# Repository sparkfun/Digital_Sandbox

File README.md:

Digital_Sandbox
===============

[*SparkFun Digital Sandbox (SKU)*](https://www.sparkfun.com/products/12651)

he Digital Sandbox (DS) is a learning platform that engages both the software and hardware worlds.
It’s powered by a microcontroller that can interact with real-world inputs – like light or temperature sensors – while simultaneously controlling LEDs, motors, and other outputs. 

Repository Contents
-------------------

* **/Documentation** - Data files for the Digital Sandbox booklet
* **/Firmware** - Example code for the Digital Sandbox experiment guide
* **/Hardware** - Eagle design files (.brd, .sch)
* **/Production** - Production panel files (.brd)

Documentation
--------------
* **[Hookup Guide](https://learn.sparkfun.com/tutorials/digital-sandbox-arduino-companion)** - Basic hookup guide for the Digital SandBox.
* **[SparkFun Fritzing repo](https://github.com/sparkfun/Fritzing_Parts)** - Fritzing diagrams for SparkFun products.
* **[SparkFun 3D Model repo](https://github.com/sparkfun/3D_Models)** - 3D models of SparkFun products.
* **[SparkFun Graphical Datasheets](https://github.com/sparkfun/Graphical_Datasheets)** -Graphical Datasheets for various SparkFun products.

License Information
-------------------

This product is _**open source**_!

Please review the LICENSE.md file for license information.

If you have any questions or concerns on licensing, please contact techsupport@sparkfun.com.

Distributed as-is; no warranty is given.

- Your friends at SparkFun.

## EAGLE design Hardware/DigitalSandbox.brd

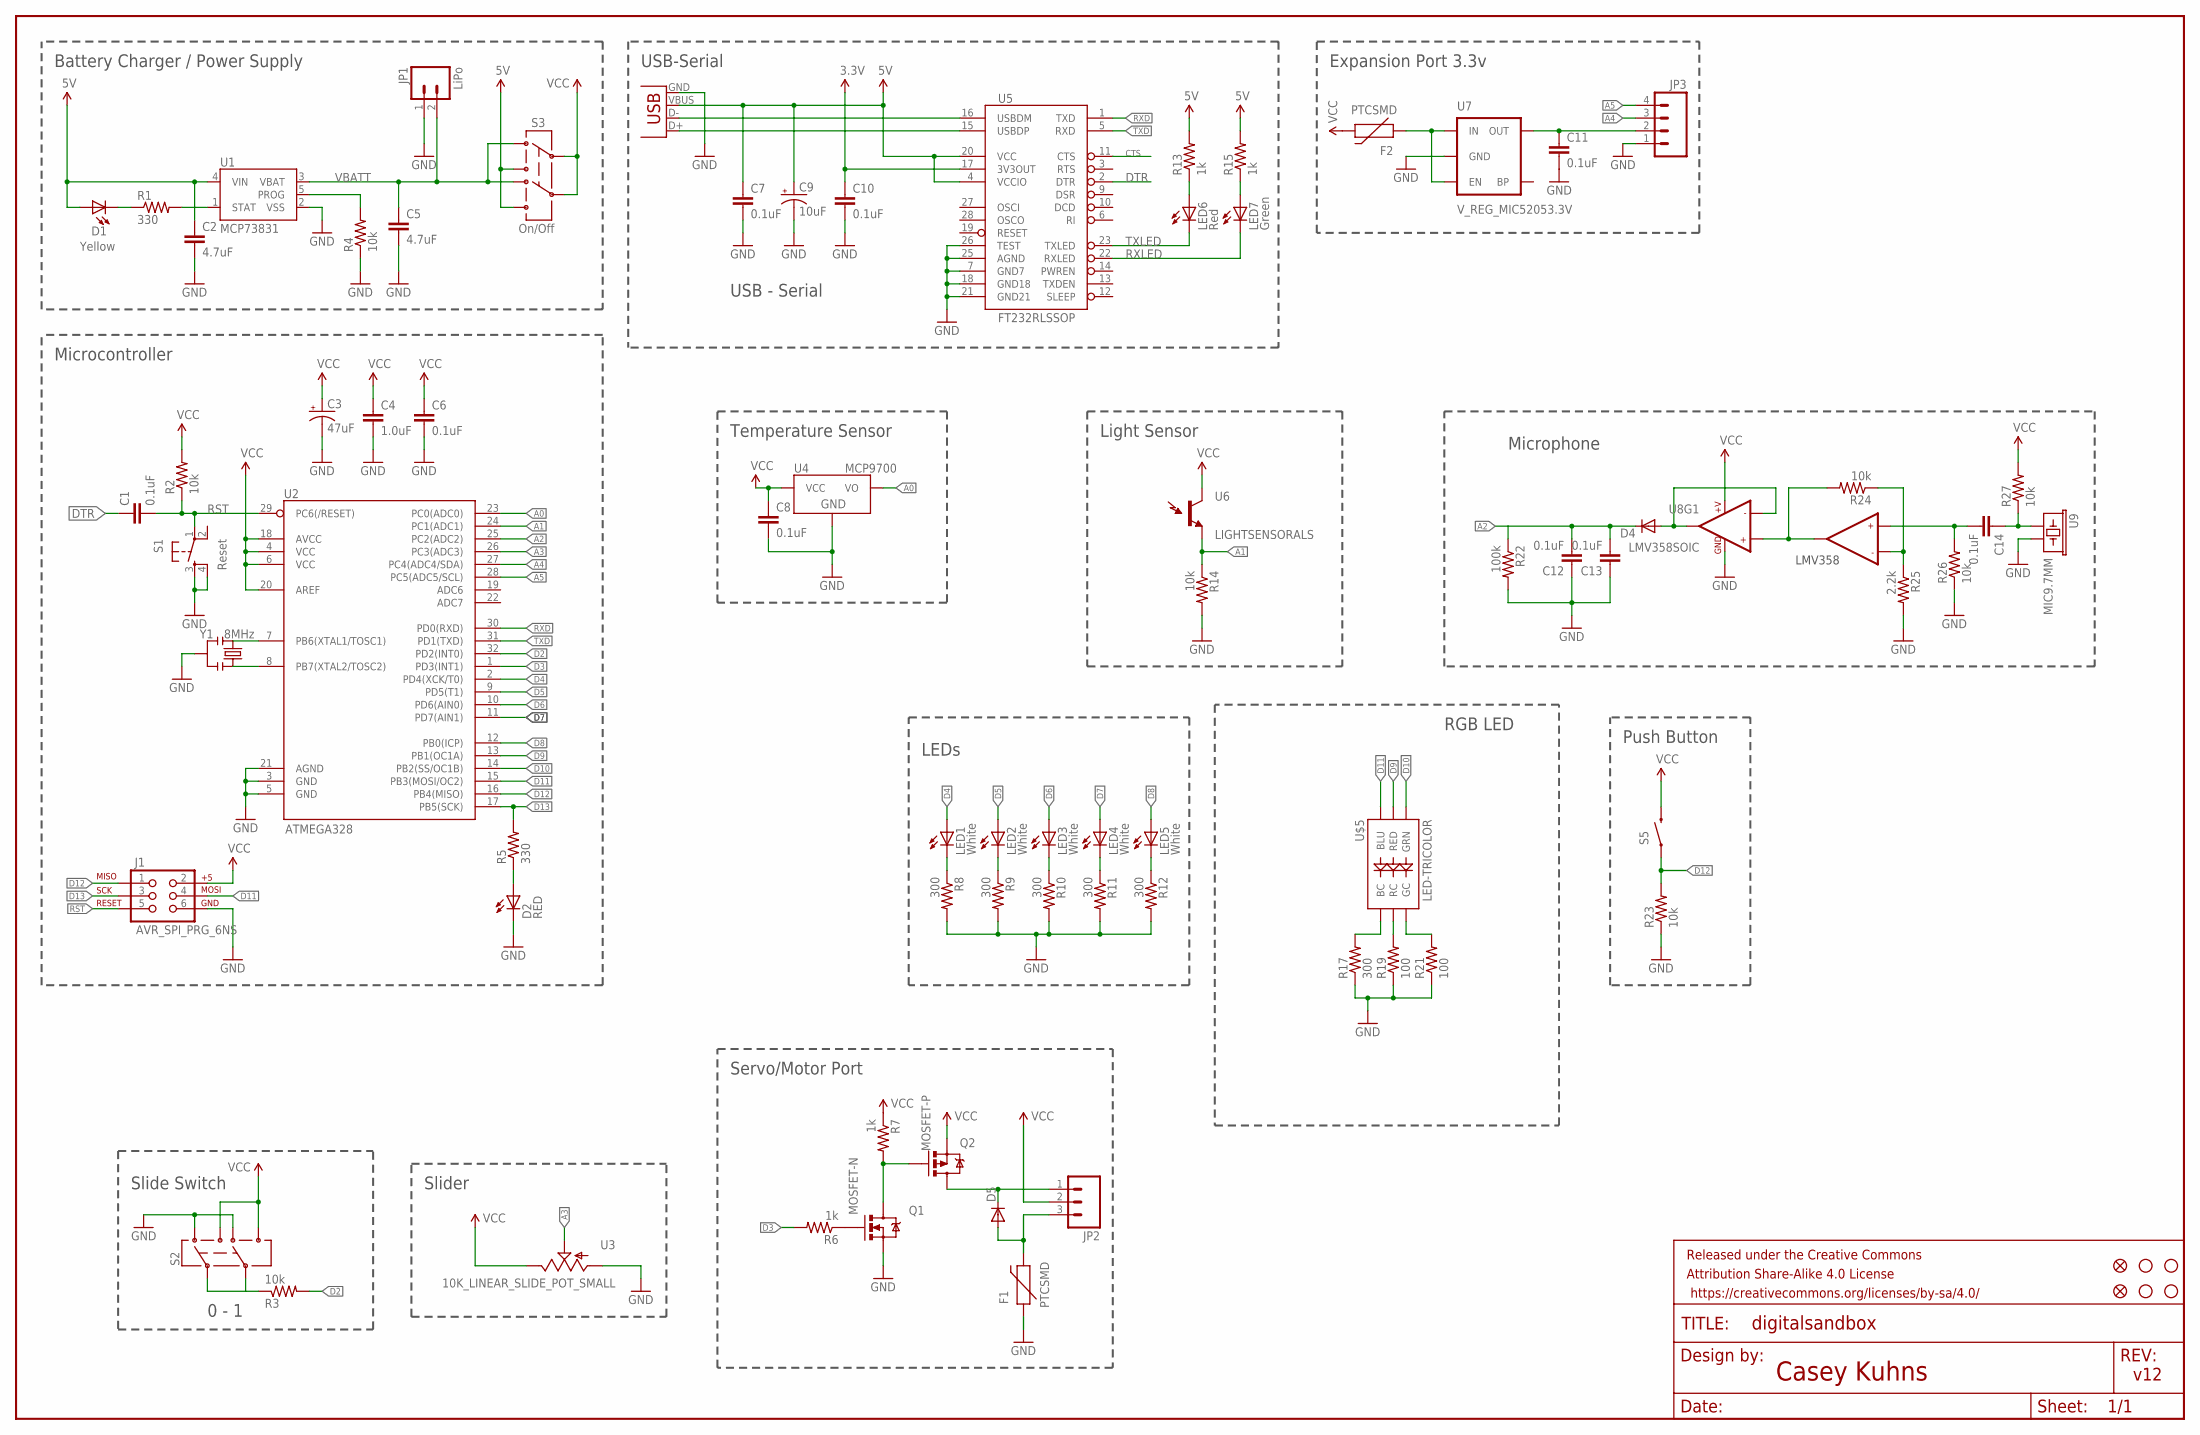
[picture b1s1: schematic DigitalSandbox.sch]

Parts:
C1, C6, C7, C8, C10, C11, C12, C13, C14: 0.1uF; 0603-CAP
C2, C5: 4.7uF; 0603-CAP
C3: 47uF; EIA3528
C4: 1.0uF; 0603-CAP
C9: 10uF; EIA3216
D1: Yellow; LED-0603
D2: RED; LED-1206
D4, D5: DIODESOD; SOD-323
F1, F2: PTCSMD; PTC-1206
FID1, FID2: FIDUCIAL1X2; FIDUCIAL-1X2
FRAME1: FRAME-LEDGER; CREATIVE_COMMONS
J1: AVR_SPI_PRG_6NS; 2X3-NS
JP1: LiPo; JST-2-SMD
JP2: M03SMD_RA_FEMALE; 1X03_SMD_RA_FEMALE
JP3: M04SMD_STRAIGHT_COMBO; 1X04_SMD_STRAIGHT_COMBO
LED1, LED2, LED3, LED4, LED5: White; LED-1206
LED6: Red; LED-0603
LED7: Green; LED-0603
Q1: MOSFET-N; SOT23
Q2: MOSFET-P; SOT23-3
R1, R5: 330; 0603-RES
R2, R3, R4, R14, R23, R24, R26, R27: 10k; 0603-RES
R6, R7, R13, R15: 1k; 0603-RES
R8, R9, R10, R11, R12, R17: 300; 0603-RES
R19, R21: 100; 0603-RES
R22: 100k; 0603-RES
R25: 2.2k; 0603-RES
S1: Reset; TACTILE_SWITCH_SMD
S2: SWITCH-DPDTAYZ0202; AYZ0202
S3: On/Off; AYZ0202
S5: SWITCH-MOMENTARY-2SMD-4; TACTILE_SWITCH_TALL
STANDOFF1, STANDOFF2, STANDOFF3, STANDOFF4: STAND-OFF
U1: MCP73831; SOT23-5
U2: ATMEGA328; TQFP32-08
U3: 10K_LINEAR_SLIDE_POT_SMALL; C2031N-1A2-B10K-GP
U4: MCP9700; SOT23-3
U5: FT232RLSSOP; SSOP28DB
U6: LIGHTSENSORALS; ALS-PT19
U7: V_REG_MIC52053.3V; SOT23-5
U8: LMV358SOIC; SO08
U9: MIC9.7MM; MIC-9.7MM
U$5: LED-TRICOLOR; PLCC-6-LED
X1: USBSMD; USB-MINIB
Y1: 8MHz; RESONATOR-SMD

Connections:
3.3V: C10.1, U5.17 (3V3OUT)
5V: C2.1, C7.1, C9.A (+), D1.A, R13.2, R15.2, S3.3, S3.6, U1.4 (VIN), U5.4 (VCCIO), U5.20 (VCC), X1.VBUS
A0: U2.23 (PC0(ADC0)), U4.2 (VO)
A1: R14.1, U2.24 (PC1(ADC1)), U6.E (E1)
A2: C12.2, C13.2, D4.C, R22.1, U2.25 (PC2(ADC2))
A3: U2.26 (PC3(ADC3)), U3.1 (S)
A4: JP3.3, U2.27 (PC4(ADC4/SDA))
A5: JP3.4, U2.28 (PC5(ADC5/SCL))
BLUE: R17.2, U$5.CB (BC)
CTS: U5.11 (CTS)
D2: R3.2, U2.32 (PD2(INT0))
D3: R6.2, U2.1 (PD3(INT1))
D4: LED1.A, U2.2 (PD4(XCK/T0))
D5: LED2.A, U2.9 (PD5(T1))
D6: LED3.A, U2.10 (PD6(AIN0))
D7: LED4.A, U2.11 (PD7(AIN1))
D8: LED5.A, U2.12 (PB0(ICP))
D9: U2.13 (PB1(OC1A)), U$5.AR (RED)
D10: U2.14 (PB2(SS/OC1B)), U$5.AG (GRN)
D11: J1.4, U2.15 (PB3(MOSI/OC2)), U$5.AB (BLU)
D12: J1.1, R23.2, S5.A2 (1), U2.16 (PB4(MISO))
D13: J1.3, R5.2, U2.17 (PB5(SCK))
DTR: C1.1, U5.2 (DTR)
GND: C2.2, C3.C (-), C4.2, C5.2, C6.2, C7.2, C8.2, C9.C (-), C10.2, C11.2, C12.1, C13.1, D2.C, F1.1, J1.6, JP1.1 (2), JP3.1, Q1.2 (S), R4.1, R8.2, R9.2, R10.2, R11.2, R12.2, R14.2, R17.1, R19.1, R21.1, R22.2, R23.1, R25.2, R26.1, S1.3, S1.4, S2.1, S2.4, U1.2 (VSS), U2.3 (GND), U2.5 (GND), U2.21 (AGND), U3.2 (A), U4.3 (GND), U5.7 (GND7), U5.18 (GND18), U5.21 (GND21), U5.25 (AGND), U5.26 (TEST), U7.2 (GND), U8.4 (GND), U9.2, X1.GND, Y1.2
GRN: R21.2, U$5.CG (GC)
unnamed: U2.7 (PB6(XTAL1/TOSC1)), Y1.1
unnamed: D2.A, R5.1
unnamed: U2.8 (PB7(XTAL2/TOSC2)), Y1.3
unnamed: Q1.3 (D), Q2.1 (G), R7.2
unnamed: LED6.A, R13.1
unnamed: LED7.A, R15.1
unnamed: F2.1, U7.1 (IN), U7.3 (EN)
unnamed: D5.C, JP2.1, Q2.3 (D)
unnamed: LED3.C, R10.1
unnamed: Q1.1 (G), R6.1
unnamed: LED4.C, R11.1
unnamed: C11.1, JP3.2, U7.5 (OUT)
unnamed: LED5.C, R12.1
unnamed: R3.1, S2.2, S2.5
unnamed: D5.A, F1.2, JP2.3
unnamed: C14.1, R27.1, U9.1
unnamed: LED1.C, R8.1
unnamed: C14.2, R26.2, U8.5 (+IN2)
unnamed: LED2.C, R9.1
unnamed: R24.1, R25.1, U8.6 (-IN2)
unnamed: D4.A, U8.1 (OUT1), U8.2 (-IN1)
unnamed: R24.2, U8.3 (+IN1), U8.7 (OUT2)
unnamed: D1.C, R1.1
PROG: R4.2, U1.5 (PROG)
RED: R19.2, U$5.CR (RC)
RST: C1.2, J1.5, R2.1, S1.1, U2.29 (PC6(/RESET))
RXD: U2.30 (PD0(RXD)), U5.1 (TXD)
RXLED: LED7.C, U5.22 (RXLED)
STAT: R1.2, U1.1 (STAT)
TXD: U2.31 (PD1(TXD)), U5.5 (RXD)
TXLED: LED6.C, U5.23 (TXLED)
USB_D+: U5.15 (USBDP), X1.D+
USB_D-: U5.16 (USBDM), X1.D-
VBATT: C5.1, JP1.2 (1), S3.1, S3.4, U1.3 (VBAT)
VCC: C3.A (+), C4.1, C6.1, C8.1, F2.2, J1.2, JP2.2, Q2.2 (S), R2.2, R7.1, R27.2, S2.3, S2.6, S3.2, S3.5, S5.B2 (2), U2.4 (VCC), U2.6 (VCC), U2.18 (AVCC), U2.20 (AREF), U3.3 (E), U4.1 (VCC), U6.C (C1), U8.8 (+V)

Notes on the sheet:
LMV358
Battery Charger / Power Supply
USB - Serial
Microcontroller
USB-Serial
Servo/Motor Port
Slider
Push Button
Slide Switch
RGB LED
Expansion Port 3.3v
LEDs
Temperature Sensor
Light Sensor
Microphone
Casey Kuhns
0 - 1
v12

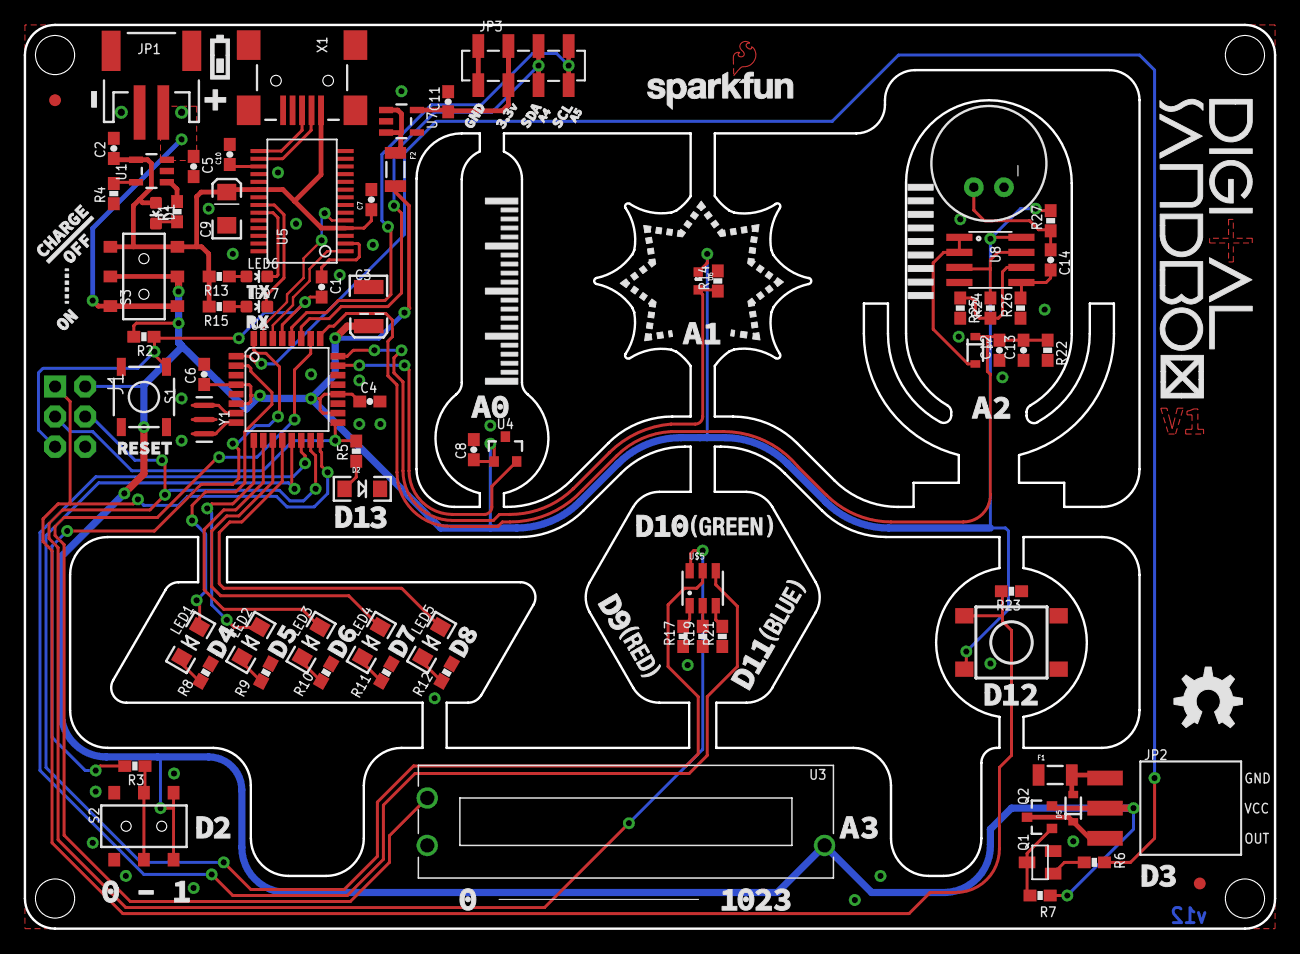
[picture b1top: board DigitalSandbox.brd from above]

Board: 2 copper layers, 105.4 x 76.2 mm, 80 parts (0 on the bottom side), 59 nets.

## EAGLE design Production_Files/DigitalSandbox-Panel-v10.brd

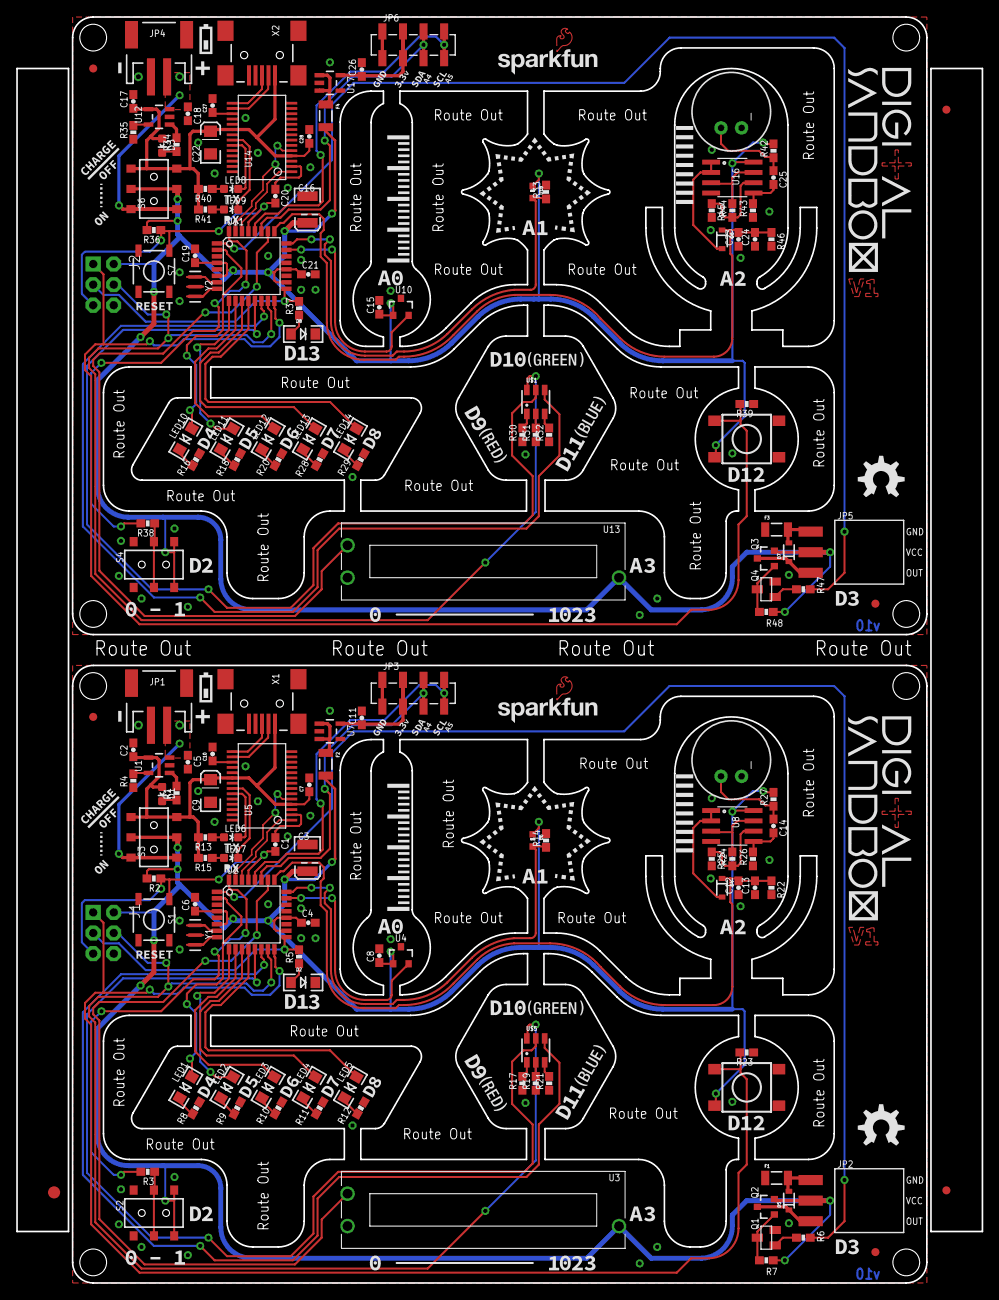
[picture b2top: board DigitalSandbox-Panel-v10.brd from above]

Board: 2 copper layers, 119.1 x 156.2 mm, 161 parts (0 on the bottom side), 118 nets.

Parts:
C1, C6, C7, C8, C10, C11, C12, C13, C14, C15, C19, C20, C23, C24, C25, C26, C27, C28: 0.1uF; 0603-CAP
C2, C5, C17, C18: 4.7uF; 0603-CAP
C3, C16: 47uF; EIA3528
C4, C21: 1.0uF; 0603-CAP
C9, C22: 10uF; EIA3216
D1, D3: Yellow; LED-0603
D2, D8: RED; LED-1206
D4, D5, D6, D7: SOD-323
E$1: FIDUCIAL-1.5X3
E$2, E$4: FIDUCIAL-1X2
F1, F2, F3, F4: PTCSMD; PTC-1206
FID1, FID2, FID3, FID4: FIDUCIAL1X2; FIDUCIAL-1X2
J1, J2: AVR_SPI_PRG_6NS; 2X3-NS
JP1, JP4: LiPo; JST-2-SMD
JP2, JP5: 1X03_SMD_RA_FEMALE
JP3, JP6: 1X04_SMD_STRAIGHT_COMBO
LED1, LED2, LED3, LED4, LED5, LED10, LED11, LED12, LED13, LED14: White; LED-1206
LED6, LED8: Red; LED-0603
LED7, LED9: Green; LED-0603
Q1, Q4: MOSFET-N; SOT23
Q2, Q3: MOSFET-P; SOT23-3
R1, R5, R34, R37: 330; 0603-RES
R2, R3, R4, R14, R23, R24, R26, R27, R33, R35, R36, R38, R39, R42, R43, R44: 10k; 0603-RES
R6, R7, R13, R15, R40, R41, R47, R48: 1k; 0603-RES
R8, R9, R10, R11, R12, R16, R17, R18, R20, R28, R29, R30: 300; 0603-RES
R19, R21, R31, R32: 100; 0603-RES
R22, R46: 100k; 0603-RES
R25, R45: 2.2k; 0603-RES
S1, S7: Reset; TACTILE_SWITCH_SMD
S2, S4: AYZ0202
S3, S6: On/Off; AYZ0202
S5, S8: SWITCH-MOMENTARY-2SMD-4; TACTILE_SWITCH_TALL
STANDOFF1, STANDOFF2, STANDOFF3, STANDOFF4, STANDOFF5, STANDOFF6, STANDOFF7, STANDOFF8: STAND-OFF
U1, U12: MCP73831; SOT23-5
U2, U11: ATMEGA328; TQFP32-08
U3, U13: C2031N-1A2-B10K-GP
U4, U10: MCP9700; SOT23-3
U5, U14: FT232RLSSOP; SSOP28DB
U6, U18: LIGHTSENSORALS; ALS-PT19
U7, U17: V_REG_LDOSMD; SOT23-5
U8, U16: LMV358SOIC; SO08
U9, U15: MIC9.7MM; MIC-9.7MM
U$1, U$5: LED-TRICOLOR-SMDPLCC-6-SMD; PLCC-6-LED
X1, X2: USBSMD; USB-MINIB
Y1, Y2: 8MHz; RESONATOR-SMD

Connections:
3.3V: C10.1, U5.17
3.3V1: C27.1, U14.17
5V: C2.1, C7.1, C9.A, D1.A, R13.2, R15.2, S3.3, S3.6, U1.4, U5.4, U5.20, X1.VBUS
5V1: C17.1, C22.A, C28.1, D3.A, R40.2, R41.2, S6.3, S6.6, U12.4, U14.4, U14.20, X2.VBUS
A0: U2.23, U4.2
A1: R14.1, U2.24, U6.E
A2: C12.2, C13.2, D4.C, R22.1, U2.25
A3: U2.26, U3.1
A4: JP3.3, U2.27
A5: JP3.4, U2.28
A6: C23.2, C24.2, D6.C, R46.1, U11.25
A7: U11.26, U13.1
A8: JP6.3, U11.27
A9: JP6.4, U11.28
A10: U10.2, U11.23
A11: R33.1, U11.24, U18.E
BLUE: R17.2, U$5.CB
BLUE1: R30.2, U$1.CB
D1: J2.4, U11.15, U$1.AB
D2: R3.2, U2.32
D3: R6.2, U2.1
D4: LED1.A, U2.2
D5: LED2.A, U2.9
D6: LED3.A, U2.10
D7: LED4.A, U2.11
D8: LED5.A, U2.12
D9: U2.13, U$5.AR
D10: U2.14, U$5.AG
D11: J1.4, U2.15, U$5.AB
D12: J1.1, R23.2, S5.A2, U2.16
D13: J1.3, R5.2, U2.17
D14: J2.3, R37.2, U11.17
D15: LED11.A, U11.9
D16: U11.13, U$1.AR
D17: LED12.A, U11.10
D18: U11.14, U$1.AG
D19: R38.2, U11.32
D20: R47.2, U11.1
D21: LED10.A, U11.2
D22: LED14.A, U11.12
D23: LED13.A, U11.11
D24: J2.1, R39.2, S8.A2, U11.16
DTR: C1.1, U5.2
DTR1: C20.1, U14.2
GND: C2.2, C3.C, C4.2, C5.2, C6.2, C7.2, C8.2, C9.C, C10.2, C11.2, C12.1, C13.1, D2.C, F1.1, J1.6, JP1.1, JP3.1, Q1.2, R4.1, R8.2, R9.2, R10.2, R11.2, R12.2, R14.2, R17.1, R19.1, R21.1, R22.2, R23.1, R25.2, R26.1, S1.2, S2.1, S2.4, U1.2, U2.3, U2.5, U2.21, U3.2, U4.3, U5.7, U5.18, U5.21, U5.25, U5.26, U7.2, U8.4, U9.2, X1.GND, Y1.2
GND1: C15.2, C16.C, C17.2, C18.2, C19.2, C21.2, C22.C, C23.1, C24.1, C26.2, C27.2, C28.2, D8.C, F3.1, J2.6, JP4.1, JP6.1, Q4.2, R16.2, R18.2, R20.2, R28.2, R29.2, R30.1, R31.1, R32.1, R33.2, R35.1, R39.1, R43.1, R45.2, R46.2, S4.1, S4.4, S7.2, U10.3, U11.3, U11.5, U11.21, U12.2, U13.2, U14.7, U14.18, U14.21, U14.25, U14.26, U15.2, U16.4, U17.2, X2.GND, Y2.2
GRN: R21.2, U$5.CG
GRN1: R32.2, U$1.CG
unnamed: U2.7, Y1.1
unnamed: D2.A, R5.1
unnamed: U2.8, Y1.3
unnamed: Q1.3, Q2.1, R7.2
unnamed: LED6.A, R13.1
unnamed: LED7.A, R15.1
unnamed: F2.1, U7.1, U7.3
unnamed: D5.C, JP2.1, Q2.3
unnamed: LED3.C, R10.1
unnamed: Q1.1, R6.1
unnamed: LED4.C, R11.1
unnamed: C11.1, JP3.2, U7.5
unnamed: LED5.C, R12.1
unnamed: R3.1, S2.2, S2.5
unnamed: D5.A, F1.2, JP2.3
unnamed: C14.1, R27.1, U9.1
unnamed: LED1.C, R8.1
unnamed: C14.2, R26.2, U8.5
unnamed: LED2.C, R9.1
unnamed: R24.1, R25.1, U8.6
unnamed: D4.A, U8.1, U8.2
unnamed: LED10.C, R16.1
unnamed: R24.2, U8.3, U8.7
unnamed: LED11.C, R18.1
unnamed: D8.A, R37.1
unnamed: U11.7, Y2.1
unnamed: U11.8, Y2.3
unnamed: D3.C, R34.1
unnamed: D1.C, R1.1
unnamed: LED12.C, R20.1
unnamed: LED13.C, R28.1
unnamed: LED14.C, R29.1
unnamed: R38.1, S4.2, S4.5
unnamed: LED8.A, R40.1
unnamed: LED9.A, R41.1
unnamed: C25.1, R42.1, U15.1
unnamed: C25.2, R43.2, U16.5
unnamed: R44.1, R45.1, U16.6
unnamed: D6.A, U16.1, U16.2
unnamed: R44.2, U16.3, U16.7
unnamed: D7.C, JP5.1, Q3.3
unnamed: Q3.1, Q4.3, R48.2
unnamed: Q4.1, R47.1
unnamed: C26.1, JP6.2, U17.5
unnamed: F4.1, U17.1, U17.3
unnamed: D7.A, F3.2, JP5.3
PROG: R4.2, U1.5
PROG1: R35.2, U12.5
RED: R19.2, U$5.CR
RED1: R31.2, U$1.CR
RST: C1.2, J1.5, R2.1, S1.1, U2.29
RST1: C20.2, J2.5, R36.1, S7.1, U11.29
RXD: U2.30, U5.1
RXD1: U11.30, U14.1
RXLED: LED7.C, U5.22
RXLED1: LED9.C, U14.22
STAT: R1.2, U1.1
STAT1: R34.2, U12.1
TXD: U2.31, U5.5
TXD1: U11.31, U14.5
TXLED: LED6.C, U5.23
TXLED1: LED8.C, U14.23
USB_D+: U5.15, X1.D+
USB_D+1: U14.15, X2.D+
USB_D-: U5.16, X1.D-
USB_D-1: U14.16, X2.D-
VBATT: C5.1, JP1.2, S3.1, S3.4, U1.3
VBATT1: C18.1, JP4.2, S6.1, S6.4, U12.3
VCC: C3.A, C4.1, C6.1, C8.1, F2.2, J1.2, JP2.2, Q2.2, R2.2, R7.1, R27.2, S2.3, S2.6, S3.2, S3.5, S5.B2, U2.4, U2.6, U2.18, U2.20, U3.3, U4.1, U6.C, U8.8
VCC1: C15.1, C16.A, C19.1, C21.1, F4.2, J2.2, JP5.2, Q3.2, R36.2, R42.2, R48.1, S4.3, S4.6, S6.2, S6.5, S8.B2, U10.1, U11.4, U11.6, U11.18, U11.20, U13.3, U16.8, U18.C

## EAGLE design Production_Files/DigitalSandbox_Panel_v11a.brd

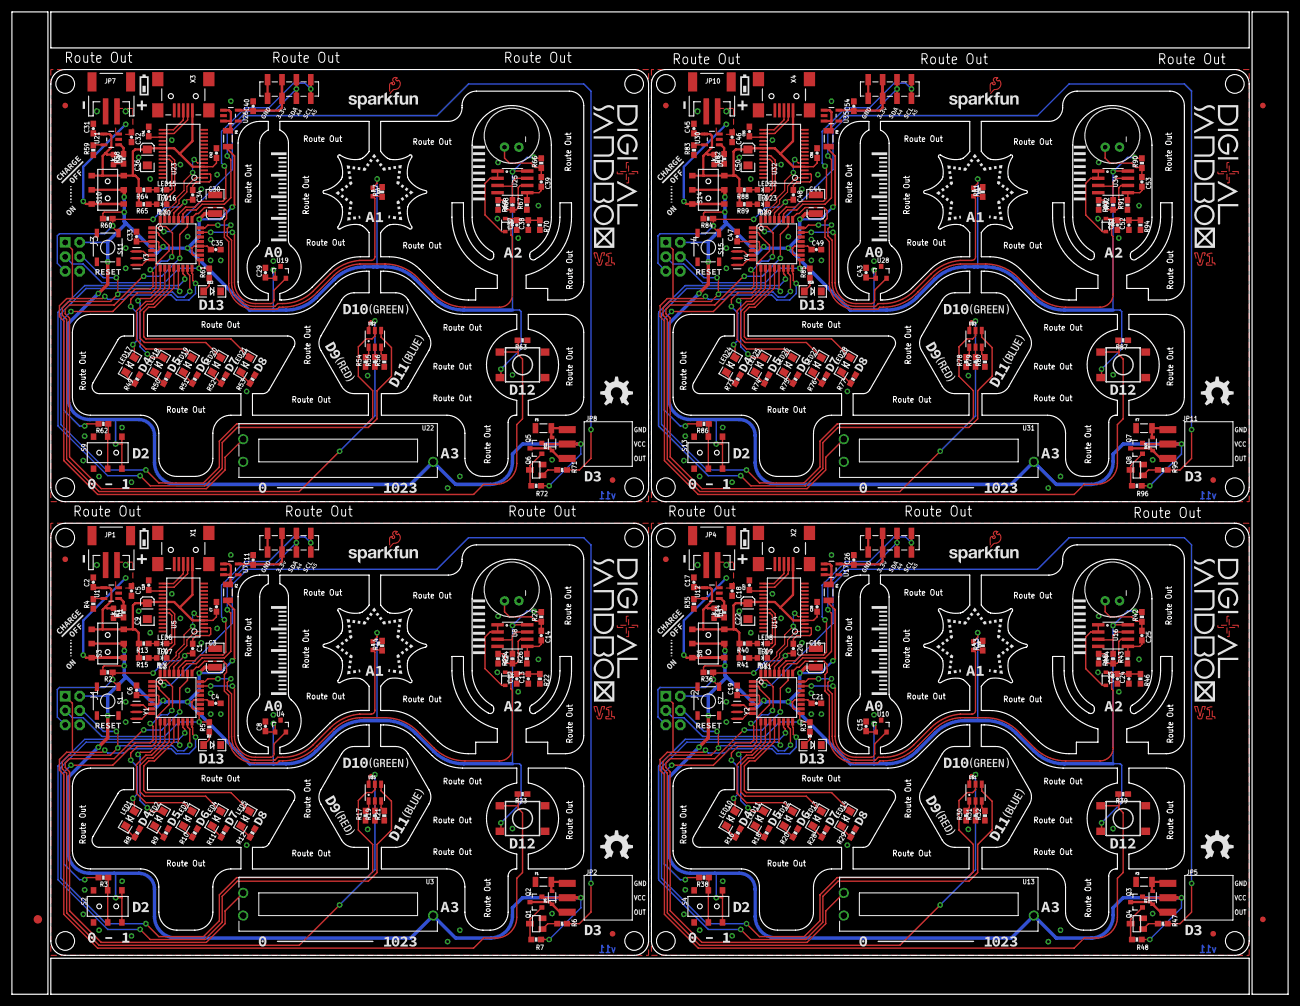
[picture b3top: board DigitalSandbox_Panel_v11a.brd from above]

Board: 2 copper layers, 225.0 x 173.2 mm, 319 parts (0 on the bottom side), 236 nets.

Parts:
C1, C6, C7, C8, C10, C11, C12, C13, C14, C15, C19, C20, C23, C24, C25, C26, C27, C28, C29, C33, C34, C37, C38, C39, C40, C41, C42, C43, C47, C48, C51, C52, C53, C54, C55, C56: 0.1uF; 0603-CAP
C2, C5, C17, C18, C31, C32, C45, C46: 4.7uF; 0603-CAP
C3, C16, C30, C44: 47uF; EIA3528
C4, C21, C35, C49: 1.0uF; 0603-CAP
C9, C22, C36, C50: 10uF; EIA3216
D1, D3, D9, D13: Yellow; LED-0603
D2, D8, D12, D16: RED; LED-1206
D4, D5, D6, D7, D10, D11, D14, D15: SOD-323
E$1: FIDUCIAL-1.5X3
E$4, E$5: FIDUCIAL-1X2
F1, F2, F3, F4, F5, F6, F7, F8: PTCSMD; PTC-1206
FID1, FID2, FID3, FID4, FID5, FID6, FID7, FID8: FIDUCIAL1X2; FIDUCIAL-1X2
J1, J2, J3, J4: AVR_SPI_PRG_6NS; 2X3-NS
JP1, JP4, JP7, JP10: LiPo; JST-2-SMD
JP2, JP5, JP8, JP11: 1X03_SMD_RA_FEMALE
JP3, JP6, JP9, JP12: 1X04_SMD_STRAIGHT_COMBO
LED1, LED2, LED3, LED4, LED5, LED10, LED11, LED12, LED13, LED14, LED17, LED18, LED19, LED20, LED21, LED24, LED25, LED26, LED27, LED28: White; LED-1206
LED6, LED8, LED15, LED22: Red; LED-0603
LED7, LED9, LED16, LED23: Green; LED-0603
Q1, Q4, Q6, Q8: MOSFET-N; SOT23
Q2, Q3, Q5, Q7: MOSFET-P; SOT23-3
R1, R5, R34, R37, R58, R61, R82, R85: 330; 0603-RES
R2, R3, R4, R14, R23, R24, R26, R27, R33, R35, R36, R38, R39, R42, R43, R44, R57, R59, R60, R62, R63, R66, R67, R68, R81, R83, R84, R86, R87, R90, R91, R92: 10k; 0603-RES
R6, R7, R13, R15, R40, R41, R47, R48, R64, R65, R71, R72, R88, R89, R95, R96: 1k; 0603-RES
R8, R9, R10, R11, R12, R16, R17, R18, R20, R28, R29, R30, R49, R50, R51, R52, R53, R54, R73, R74, R75, R76, R77, R78: 300; 0603-RES
R19, R21, R31, R32, R55, R56, R79, R80: 100; 0603-RES
R22, R46, R70, R94: 100k; 0603-RES
R25, R45, R69, R93: 2.2k; 0603-RES
S1, S7, S11, S15: Reset; TACTILE_SWITCH_SMD
S2, S4, S9, S13: AYZ0202
S3, S6, S10, S14: On/Off; AYZ0202
S5, S8, S12, S16: SWITCH-MOMENTARY-2SMD-4; TACTILE_SWITCH_TALL
STANDOFF1, STANDOFF2, STANDOFF3, STANDOFF4, STANDOFF5, STANDOFF6, STANDOFF7, STANDOFF8, STANDOFF9, STANDOFF10, STANDOFF11, STANDOFF12, STANDOFF13, STANDOFF14, STANDOFF15, STANDOFF16: STAND-OFF
U1, U12, U21, U30: MCP73831; SOT23-5
U2, U11, U20, U29: ATMEGA328; TQFP32-08
U3, U13, U22, U31: 10K_LINEAR_SLIDE_POT_SMALL; C2031N-1A2-B10K-GP
U4, U10, U19, U28: MCP9700; SOT23-3
U5, U14, U23, U32: FT232RLSSOP; SSOP28DB
U6, U18, U27, U36: LIGHTSENSORALS; ALS-PT19
U7, U17, U26, U35: V_REG_MIC52053.3V; SOT23-5
U8, U16, U25, U34: LMV358SOIC; SO08
U9, U15, U24, U33: MIC9.7MM; MIC-9.7MM
U$1, U$2, U$3, U$5: LED-TRICOLOR; PLCC-6-LED
X1, X2, X3, X4: USBSMD; USB-MINIB
Y1, Y2, Y3, Y4: 8MHz; RESONATOR-SMD

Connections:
3.3V: C10.1, U5.17
3.3V1: C27.1, U14.17
3.3V2: C41.1, U23.17
3.3V3: C55.1, U32.17
5V: C2.1, C7.1, C9.A, D1.A, R13.2, R15.2, S3.3, S3.6, U1.4, U5.4, U5.20, X1.VBUS
5V1: C17.1, C22.A, C28.1, D3.A, R40.2, R41.2, S6.3, S6.6, U12.4, U14.4, U14.20, X2.VBUS
5V2: C31.1, C36.A, C42.1, D9.A, R64.2, R65.2, S10.3, S10.6, U21.4, U23.4, U23.20, X3.VBUS
5V3: C45.1, C50.A, C56.1, D13.A, R88.2, R89.2, S14.3, S14.6, U30.4, U32.4, U32.20, X4.VBUS
A0: U2.23, U4.2
A1: R14.1, U2.24, U6.E
A2: C12.2, C13.2, D4.C, R22.1, U2.25
A3: U2.26, U3.1
A4: JP3.3, U2.27
A5: JP3.4, U2.28
A6: C23.2, C24.2, D6.C, R46.1, U11.25
A7: U11.26, U13.1
A8: JP6.3, U11.27
A9: JP6.4, U11.28
A10: U10.2, U11.23
A11: R33.1, U11.24, U18.E
A12: C37.2, C38.2, D10.C, R70.1, U20.25
A13: U20.26, U22.1
A14: JP9.3, U20.27
A15: JP9.4, U20.28
A16: U19.2, U20.23
A17: R57.1, U20.24, U27.E
A18: C51.2, C52.2, D14.C, R94.1, U29.25
A19: U29.26, U31.1
A20: JP12.3, U29.27
A21: JP12.4, U29.28
A22: U28.2, U29.23
A23: R81.1, U29.24, U36.E
BLUE: R17.2, U$5.CB
BLUE1: R30.2, U$1.CB
BLUE2: R54.2, U$2.CB
BLUE3: R78.2, U$3.CB
D1: J2.4, U11.15, U$1.AB
D2: R3.2, U2.32
D3: R6.2, U2.1
D4: LED1.A, U2.2
D5: LED2.A, U2.9
D6: LED3.A, U2.10
D7: LED4.A, U2.11
D8: LED5.A, U2.12
D9: U2.13, U$5.AR
D10: U2.14, U$5.AG
D11: J1.4, U2.15, U$5.AB
D12: J1.1, R23.2, S5.A2, U2.16
D13: J1.3, R5.2, U2.17
D14: J2.3, R37.2, U11.17
D15: LED11.A, U11.9
D16: U11.13, U$1.AR
D17: LED12.A, U11.10
D18: U11.14, U$1.AG
D19: R38.2, U11.32
D20: R47.2, U11.1
D21: LED10.A, U11.2
D22: LED14.A, U11.12
D23: LED13.A, U11.11
D24: J2.1, R39.2, S8.A2, U11.16
D25: J3.4, U20.15, U$2.AB
D26: J3.3, R61.2, U20.17
D27: LED18.A, U20.9
D28: U20.13, U$2.AR
D29: LED19.A, U20.10
D30: U20.14, U$2.AG
D31: R62.2, U20.32
D32: R71.2, U20.1
D33: LED17.A, U20.2
D34: LED21.A, U20.12
D35: LED20.A, U20.11
D36: J3.1, R63.2, S12.A2, U20.16
D37: J4.4, U29.15, U$3.AB
D38: J4.3, R85.2, U29.17
D39: LED25.A, U29.9
D40: U29.13, U$3.AR
D41: LED26.A, U29.10
D42: U29.14, U$3.AG
D43: R86.2, U29.32
D44: R95.2, U29.1
D45: LED24.A, U29.2
D46: LED28.A, U29.12
D47: LED27.A, U29.11
D48: J4.1, R87.2, S16.A2, U29.16
DTR: C1.1, U5.2
DTR1: C20.1, U14.2
DTR2: C34.1, U23.2
DTR3: C48.1, U32.2
GND: C2.2, C3.C, C4.2, C5.2, C6.2, C7.2, C8.2, C9.C, C10.2, C11.2, C12.1, C13.1, D2.C, F1.1, J1.6, JP1.1, JP3.1, Q1.2, R4.1, R8.2, R9.2, R10.2, R11.2, R12.2, R14.2, R17.1, R19.1, R21.1, R22.2, R23.1, R25.2, R26.1, S1.3, S1.4, S2.1, S2.4, U1.2, U2.3, U2.5, U2.21, U3.2, U4.3, U5.7, U5.18, U5.21, U5.25, U5.26, U7.2, U8.4, U9.2, X1.GND, Y1.2
GND1: C15.2, C16.C, C17.2, C18.2, C19.2, C21.2, C22.C, C23.1, C24.1, C26.2, C27.2, C28.2, D8.C, F3.1, J2.6, JP4.1, JP6.1, Q4.2, R16.2, R18.2, R20.2, R28.2, R29.2, R30.1, R31.1, R32.1, R33.2, R35.1, R39.1, R43.1, R45.2, R46.2, S4.1, S4.4, S7.3, S7.4, U10.3, U11.3, U11.5, U11.21, U12.2, U13.2, U14.7, U14.18, U14.21, U14.25, U14.26, U15.2, U16.4, U17.2, X2.GND, Y2.2
GND2: C29.2, C30.C, C31.2, C32.2, C33.2, C35.2, C36.C, C37.1, C38.1, C40.2, C41.2, C42.2, D12.C, F5.1, J3.6, JP7.1, JP9.1, Q6.2, R49.2, R50.2, R51.2, R52.2, R53.2, R54.1, R55.1, R56.1, R57.2, R59.1, R63.1, R67.1, R69.2, R70.2, S9.1, S9.4, S11.3, S11.4, U19.3, U20.3, U20.5, U20.21, U21.2, U22.2, U23.7, U23.18, U23.21, U23.25, U23.26, U24.2, U25.4, U26.2, X3.GND, Y3.2
GND3: C43.2, C44.C, C45.2, C46.2, C47.2, C49.2, C50.C, C51.1, C52.1, C54.2, C55.2, C56.2, D16.C, F7.1, J4.6, JP10.1, JP12.1, Q8.2, R73.2, R74.2, R75.2, R76.2, R77.2, R78.1, R79.1, R80.1, R81.2, R83.1, R87.1, R91.1, R93.2, R94.2, S13.1, S13.4, S15.3, S15.4, U28.3, U29.3, U29.5, U29.21, U30.2, U31.2, U32.7, U32.18, U32.21, U32.25, U32.26, U33.2, U34.4, U35.2, X4.GND, Y4.2
GRN: R21.2, U$5.CG
GRN1: R32.2, U$1.CG
GRN2: R56.2, U$2.CG
GRN3: R80.2, U$3.CG
unnamed: U2.7, Y1.1
unnamed: D2.A, R5.1
unnamed: U2.8, Y1.3
unnamed: Q1.3, Q2.1, R7.2
unnamed: LED6.A, R13.1
unnamed: LED7.A, R15.1
unnamed: F2.1, U7.1, U7.3
unnamed: D5.C, JP2.1, Q2.3
unnamed: LED3.C, R10.1
unnamed: Q1.1, R6.1
unnamed: LED4.C, R11.1
unnamed: C11.1, JP3.2, U7.5
unnamed: LED5.C, R12.1
unnamed: R3.1, S2.2, S2.5
unnamed: D5.A, F1.2, JP2.3
unnamed: C14.1, R27.1, U9.1
unnamed: LED1.C, R8.1
unnamed: C14.2, R26.2, U8.5
unnamed: LED2.C, R9.1
unnamed: R24.1, R25.1, U8.6
unnamed: D4.A, U8.1, U8.2
unnamed: LED10.C, R16.1
unnamed: R24.2, U8.3, U8.7
unnamed: LED11.C, R18.1
unnamed: D8.A, R37.1
unnamed: U11.7, Y2.1
unnamed: U11.8, Y2.3
unnamed: D3.C, R34.1
unnamed: D1.C, R1.1
unnamed: LED12.C, R20.1
unnamed: LED13.C, R28.1
unnamed: LED14.C, R29.1
unnamed: R38.1, S4.2, S4.5
unnamed: LED8.A, R40.1
unnamed: LED9.A, R41.1
unnamed: C25.1, R42.1, U15.1
unnamed: C25.2, R43.2, U16.5
unnamed: R44.1, R45.1, U16.6
unnamed: D6.A, U16.1, U16.2
unnamed: R44.2, U16.3, U16.7
unnamed: D7.C, JP5.1, Q3.3
unnamed: Q3.1, Q4.3, R48.2
unnamed: Q4.1, R47.1
unnamed: C26.1, JP6.2, U17.5
unnamed: F4.1, U17.1, U17.3
unnamed: D7.A, F3.2, JP5.3
unnamed: LED17.C, R49.1
unnamed: LED18.C, R50.1
unnamed: D12.A, R61.1
unnamed: U20.7, Y3.1
unnamed: U20.8, Y3.3
unnamed: D9.C, R58.1
unnamed: LED19.C, R51.1
unnamed: LED20.C, R52.1
unnamed: LED21.C, R53.1
unnamed: R62.1, S9.2, S9.5
unnamed: LED15.A, R64.1
unnamed: LED16.A, R65.1
unnamed: C39.1, R66.1, U24.1
unnamed: C39.2, R67.2, U25.5
unnamed: R68.1, R69.1, U25.6
unnamed: D10.A, U25.1, U25.2
unnamed: R68.2, U25.3, U25.7
unnamed: D11.C, JP8.1, Q5.3
unnamed: Q5.1, Q6.3, R72.2
unnamed: Q6.1, R71.1
unnamed: C40.1, JP9.2, U26.5
unnamed: F6.1, U26.1, U26.3
unnamed: D11.A, F5.2, JP8.3
unnamed: LED24.C, R73.1
unnamed: LED25.C, R74.1
unnamed: D16.A, R85.1
unnamed: U29.7, Y4.1
unnamed: U29.8, Y4.3
unnamed: D13.C, R82.1
unnamed: LED26.C, R75.1
unnamed: LED27.C, R76.1
unnamed: LED28.C, R77.1
unnamed: R86.1, S13.2, S13.5
unnamed: LED22.A, R88.1
unnamed: LED23.A, R89.1
unnamed: C53.1, R90.1, U33.1
unnamed: C53.2, R91.2, U34.5
unnamed: R92.1, R93.1, U34.6
unnamed: D14.A, U34.1, U34.2
unnamed: R92.2, U34.3, U34.7
unnamed: D15.C, JP11.1, Q7.3
unnamed: Q7.1, Q8.3, R96.2
unnamed: Q8.1, R95.1
unnamed: C54.1, JP12.2, U35.5
unnamed: F8.1, U35.1, U35.3
unnamed: D15.A, F7.2, JP11.3
PROG: R4.2, U1.5
PROG1: R35.2, U12.5
PROG2: R59.2, U21.5
PROG3: R83.2, U30.5
RED: R19.2, U$5.CR
RED1: R31.2, U$1.CR
RED2: R55.2, U$2.CR
RED3: R79.2, U$3.CR
RST: C1.2, J1.5, R2.1, S1.1, U2.29
RST1: C20.2, J2.5, R36.1, S7.1, U11.29
RST2: C34.2, J3.5, R60.1, S11.1, U20.29
RST3: C48.2, J4.5, R84.1, S15.1, U29.29
RXD: U2.30, U5.1
RXD1: U11.30, U14.1
RXD2: U20.30, U23.1
RXD3: U29.30, U32.1
RXLED: LED7.C, U5.22
RXLED1: LED9.C, U14.22
RXLED2: LED16.C, U23.22
RXLED3: LED23.C, U32.22
STAT: R1.2, U1.1
STAT1: R34.2, U12.1
STAT2: R58.2, U21.1
STAT3: R82.2, U30.1
TXD: U2.31, U5.5
TXD1: U11.31, U14.5
TXD2: U20.31, U23.5
TXD3: U29.31, U32.5
TXLED: LED6.C, U5.23
TXLED1: LED8.C, U14.23
TXLED2: LED15.C, U23.23
TXLED3: LED22.C, U32.23
USB_D+: U5.15, X1.D+
USB_D+1: U14.15, X2.D+
USB_D+2: U23.15, X3.D+
USB_D+3: U32.15, X4.D+
USB_D-: U5.16, X1.D-
USB_D-1: U14.16, X2.D-
USB_D-2: U23.16, X3.D-
USB_D-3: U32.16, X4.D-
VBATT: C5.1, JP1.2, S3.1, S3.4, U1.3
VBATT1: C18.1, JP4.2, S6.1, S6.4, U12.3
VBATT2: C32.1, JP7.2, S10.1, S10.4, U21.3
VBATT3: C46.1, JP10.2, S14.1, S14.4, U30.3
VCC: C3.A, C4.1, C6.1, C8.1, F2.2, J1.2, JP2.2, Q2.2, R2.2, R7.1, R27.2, S2.3, S2.6, S3.2, S3.5, S5.B2, U2.4, U2.6, U2.18, U2.20, U3.3, U4.1, U6.C, U8.8
VCC1: C15.1, C16.A, C19.1, C21.1, F4.2, J2.2, JP5.2, Q3.2, R36.2, R42.2, R48.1, S4.3, S4.6, S6.2, S6.5, S8.B2, U10.1, U11.4, U11.6, U11.18, U11.20, U13.3, U16.8, U18.C
VCC2: C29.1, C30.A, C33.1, C35.1, F6.2, J3.2, JP8.2, Q5.2, R60.2, R66.2, R72.1, S9.3, S9.6, S10.2, S10.5, S12.B2, U19.1, U20.4, U20.6, U20.18, U20.20, U22.3, U25.8, U27.C
VCC3: C43.1, C44.A, C47.1, C49.1, F8.2, J4.2, JP11.2, Q7.2, R84.2, R90.2, R96.1, S13.3, S13.6, S14.2, S14.5, S16.B2, U28.1, U29.4, U29.6, U29.18, U29.20, U31.3, U34.8, U36.C

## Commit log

2013-10-28 Added files for board.
    Will be handing off to marcom for futrther silk work.
2013-10-28 Fixed file structure
2013-10-28 Removed problem files
2013-11-13 Modified layout according to design review findings. Still working on silk.
2013-11-21 Added silk and moved some components
2013-11-21 fixed numbering issues with resistors
2013-11-21 Added Mosfets and updated numbering
2013-11-22 fixed border width
2013-12-28 Changes Made: 1. Swap Tx-Rx 3. correct stop mask on 2 exposed vias 6. flip default logic for push button (Currently normally high) 9. Change i2c header to meet new standard in the works.
    TODO:
    2. Make programming vias for Production
    4. reverse the direction of the potentiometer and add silk showing "0 - 1024"
    5. Source new push button
    7. Investigate adding pulldown resistors for the nchannel fets that service the RGB led
    8. Investigate a new resistor value for the light sensor to increase sensitivity.
2014-01-14 Changes Made
    1. Made programming vias for Production
    2. reversed the direction of the potentiometer and added silk showing "0 - 1024"
    3. Replaced Mosfets with NPN transistors to control RGB led
    4. Replaces Light sensor with one used on Weather Shield IC-11836
    5. Labeled pin 13 LED (near the uC).
    TODO
2014-01-14 added local fiducials
2014-01-20 added ISP header
2014-01-20 added fixed files
2014-01-21 corrected silk and moved vias to prevent ground plane breaks. Touched up layout of schematic to add tags and remove confusing junctions
2014-01-23 Added testpoints for battery charger
2014-01-23 modified Transistor names to reflect BOM I will add a new part the the LIB soon
2014-02-13 Corrected drill hit on power trace.
2014-03-25 Completed:
    1. D13 led from 0603 yellow to 1206 Red.
    2. Re-order A0 - A2.
    3. Add Flyback diode on Motor port
    4. Change resistor values on LED row to 330ohm to reduce intensity.
    6. Label D3 output for motors and servos
    7. Replace D12 pushbutton with new raised head button.
2014-04-08 removed power transistors from RGB LED's.
2014-04-08 added Rev number
2014-04-14 reduced size of board by .15 inch in X
2014-04-15 fixed silk
2014-04-15 fixed akward spacing on wires
2014-04-15 moved flame
2014-04-21 Added Sparkle Values.
2014-04-22 created panel v10
2014-05-01 updated Sparkle ID's
2014-05-07 Adding Documentation Files
    The XML files in the DS Guide Content folder can be updated with new
    changes that will go in the DS guide. Using the Import XML feature in
    InDesign, the DS guide can be quickly updated with changes.
2014-05-12 Updated Intro Section
2014-08-04 fixed reset button orientation to work with standard push button
2014-08-05 created panel v11
2015-02-06 fix a small gap in the dimension layer
2015-07-13 created larger panel (v11a)
2015-11-25 Chg to v12, thicken logo/art borders
2015-11-25 V12, chg silk/cpr/mask logos and art to 0.003in
2016-11-03 Adding example sketches from hookup guide, fixing .git files, updating readme

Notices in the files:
parts and their libraries:
SparkFun-Aesthetics: Licensing: CC v3.0 Share-Alike You are welcome to use this library for commercial purposes.
SparkFun-Aesthetics: Released under the Creative Commons Attribution Share-Alike 4.0 License
SparkFun-Aesthetics: https://creativecommons.org/licenses/by-sa/4.0
